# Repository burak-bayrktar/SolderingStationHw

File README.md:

# SolderingStationHw
Soldering iron station based on stm32f030

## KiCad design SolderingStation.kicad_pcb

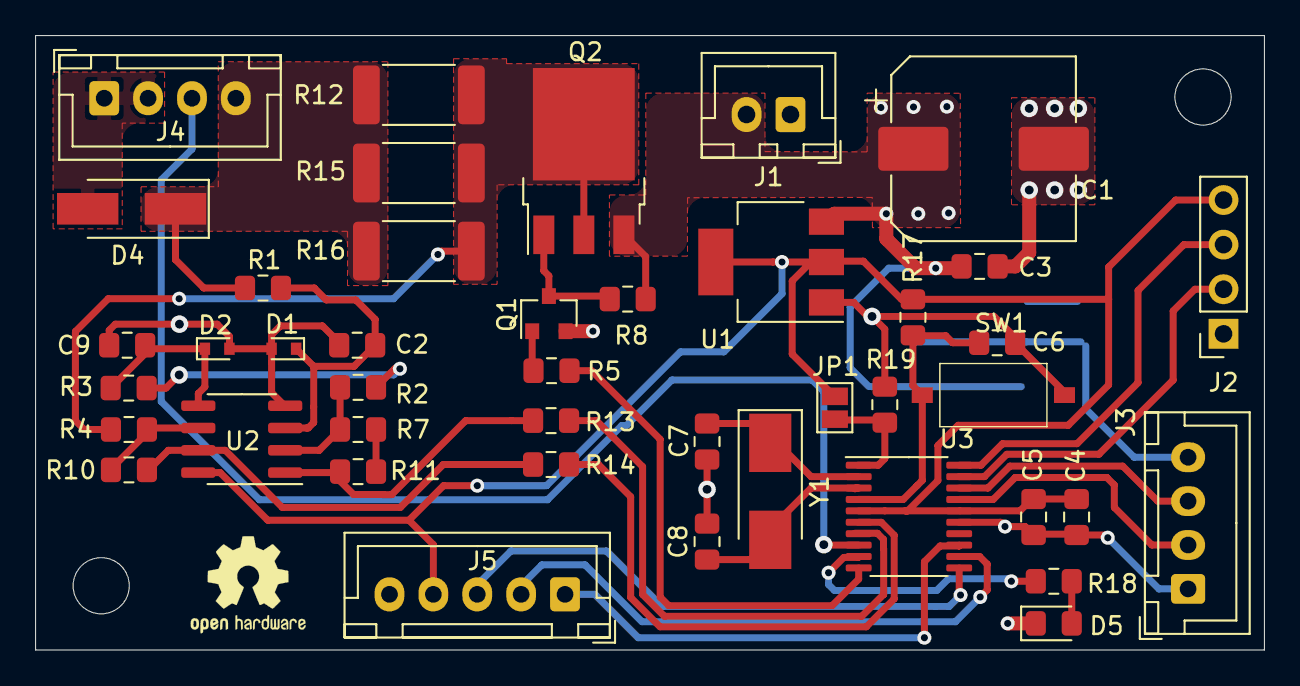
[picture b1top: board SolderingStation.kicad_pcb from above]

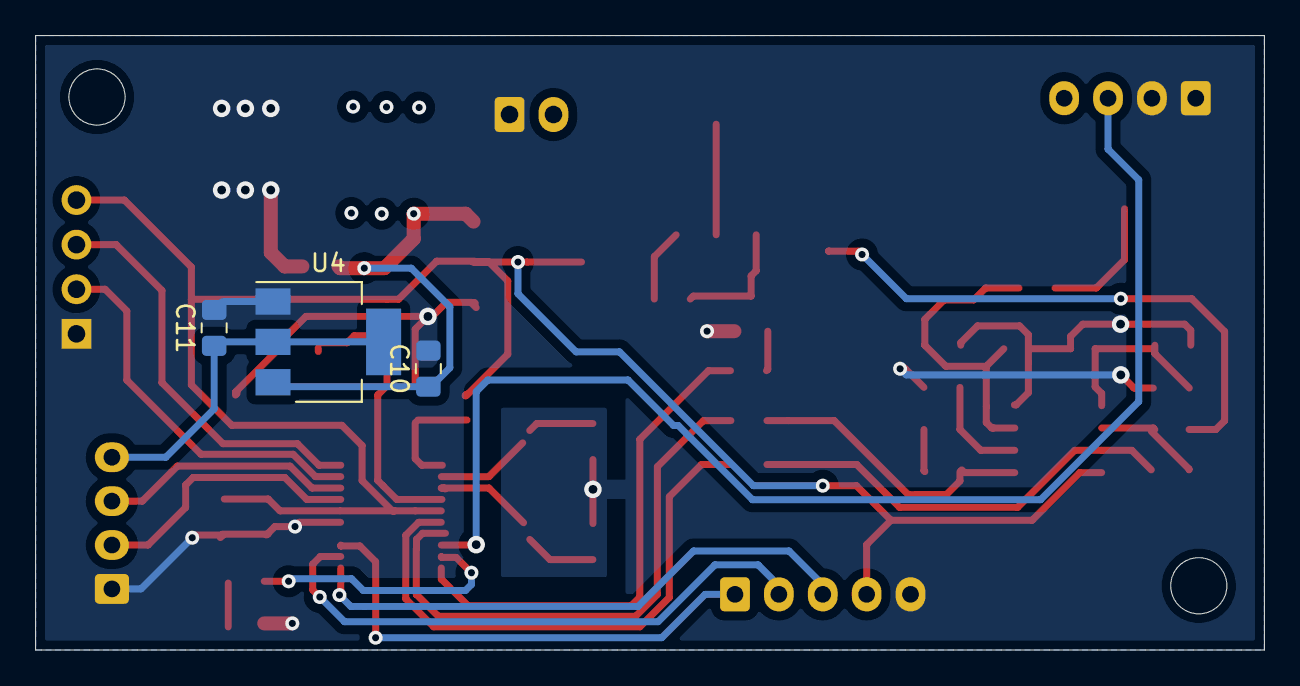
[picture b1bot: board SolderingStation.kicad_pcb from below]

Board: 2 copper layers, 70.0 x 35.0 mm, 46 parts (3 on the bottom side), 32 nets.

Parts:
C1: CP; CP_Elec_10x10
C2, C3, C5, C9, C10: 100nF; C_0805_2012Metric_Pad1.15x1.40mm_HandSolder
C4, C11: 10uF; C_0805_2012Metric_Pad1.15x1.40mm_HandSolder
C6: 100nf; C_0805_2012Metric_Pad1.15x1.40mm_HandSolder
C7, C8: 27pF; C_0805_2012Metric_Pad1.15x1.40mm_HandSolder
D1, D2: 3V3; D_SOD-523
D4: D; D_SMA_Handsoldering
D5: LED; LED_0805_2012Metric_Pad1.15x1.40mm_HandSolder
J1: POWER; JST_XH_B2B-XH-A_1x02_P2.50mm_Vertical
J2: SW; PinSocket_1x04_P2.54mm_Vertical
J3: I2C; JST_XH_B4B-XH-A_1x04_P2.50mm_Vertical
J4: IRON; JST_XH_B4B-XH-A_1x04_P2.50mm_Vertical
J5: ENCODER; JST_XH_B5B-XH-A_1x05_P2.50mm_Vertical
JP1: BOOT; SolderJumper-2_P1.3mm_Open_Pad1.0x1.5mm
Q1: BC817; SOT-23
Q2: Q_PMOS_GDS; TO-252-3_TabPin2
R1, R3, R5, R8: 10K; R_0805_2012Metric_Pad1.15x1.40mm_HandSolder
R2, R4: 1k; R_0805_2012Metric_Pad1.15x1.40mm_HandSolder
R7, R11: 100k; R_0805_2012Metric_Pad1.15x1.40mm_HandSolder
R10: 10k; R_0805_2012Metric_Pad1.15x1.40mm_HandSolder
R12, R15, R16: R22; R_2512_6332Metric_Pad1.52x3.35mm_HandSolder
R13, R14: 470K; R_0805_2012Metric_Pad1.15x1.40mm_HandSolder
R17, R18: R; R_0805_2012Metric_Pad1.15x1.40mm_HandSolder
R19: 1K; R_0805_2012Metric_Pad1.15x1.40mm_HandSolder
SW1: SW_SPST; L-KLS7-TS3611-2.5-180-T
U1: AP1117-33; SOT-223-3_TabPin2
U2: TLC272; SOIC-8_3.9x4.9mm_P1.27mm
U3: STM32F030F4Px; TSSOP-20_4.4x6.5mm_P0.65mm
U4: AP1117-50; SOT-223-3_TabPin2
Y1: Crystal; Crystal_SMD_Abracon_ABM3-2Pin_5.0x3.2mm_HandSoldering

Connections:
+3V3: C4.1, C5.1, J2.4, J5.4, JP1.1, R17.2, U1.2, U2.8, U3.5, U3.16
+5V: C11.1, J3.4, U4.2
+24V: C1.1, C3.1, C10.1, J1.2, Q2.3, R8.2, U1.3, U4.3
BOOT: JP1.2, R19.2, U3.1
CURR: R14.1, U3.6
ENC_A: J5.3, U3.11
ENC_B: J5.2, U3.12
ENC_BTN: J5.1, U3.13
GND: C1.2, C2.2, C3.2, C4.2, C5.2, C6.2, C7.2, C8.2, C9.2, C10.2, C11.2, D1.2, D2.2, D4.2, D5.1, J1.1, J2.1, J3.1, J4.1, J4.2, J5.5, Q1.2, R2.2, R3.2, R19.1, SW1.2, U1.1, U2.4, U3.15, U4.1
IRON_P: D4.1, J4.4, R1.2, R12.2, R15.2, R16.2
unnamed: C2.1, D1.1, R1.1, U2.3
unnamed: C9.1, D2.1, R3.1, U2.5
unnamed: D5.2, R18.1
unnamed: Q1.1, R5.1
unnamed: Q1.3, Q2.1, R8.1
unnamed: R2.1, R7.2, U2.2
unnamed: R10.1, R14.2, U2.7
unnamed: R4.1, R10.2, U2.6
unnamed: R11.1, R13.2, U2.1
unnamed: R7.1, R11.2
PA3: R18.2, U3.9
PWM: R5.2, U3.10
RST: C6.1, R17.1, SW1.1, U3.4
SCL: J3.2, U3.17
SDA: J3.3, U3.18
SHUNT_P: Q2.2, R4.2, R12.1, R15.1, R16.1
SWDIO: J2.2, U3.19
SWSCL: J2.3, U3.20
TEMP: R13.1, U3.7
TILT: J4.3, U3.8
XTAL_IN: C7.1, U3.2, Y1.1
XTAL_OUT: C8.1, U3.3, Y1.2

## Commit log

2022-08-21 A mad change has commited
    N Channel mosfet was creating such agony that no one should ever be exposed to. Switch to P channel mos and changed the overall shape to more like a rectangle.
